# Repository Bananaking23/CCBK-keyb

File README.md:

# CCBK-keyb
I have decided to make this keyboard as I currently have a 68% keyboard and it feels bad not have f keys and home and delete, as I like to code and those keys are useful shortcuts. The switches I chose sound great and are relatively cheap. This project also improved my skills as I have only made a PCB ones (the hackpad). 

This is my berry cool 75% keyboard, it has a display, 80 keys, under-key lights, and a rotary encoder. It is powered by a rp2040 plus and uses an mcu23017 as gpio extender

# Photos

## almost full thing

for some reason i couldnt get all the keycaps on

## Scematic
### Main 

### Switch Matrix

### Led

## pcb

## Case

### Usb-c

### Plate

# BOM

### Link
https://1drv.ms/x/c/3f7de78506c0c654/IQBztQz0UetkR5LsrjEMn85vARuH-ncA3dCGhFmHGj_PK4U?e=rccWr9

#A fter completion

## Case

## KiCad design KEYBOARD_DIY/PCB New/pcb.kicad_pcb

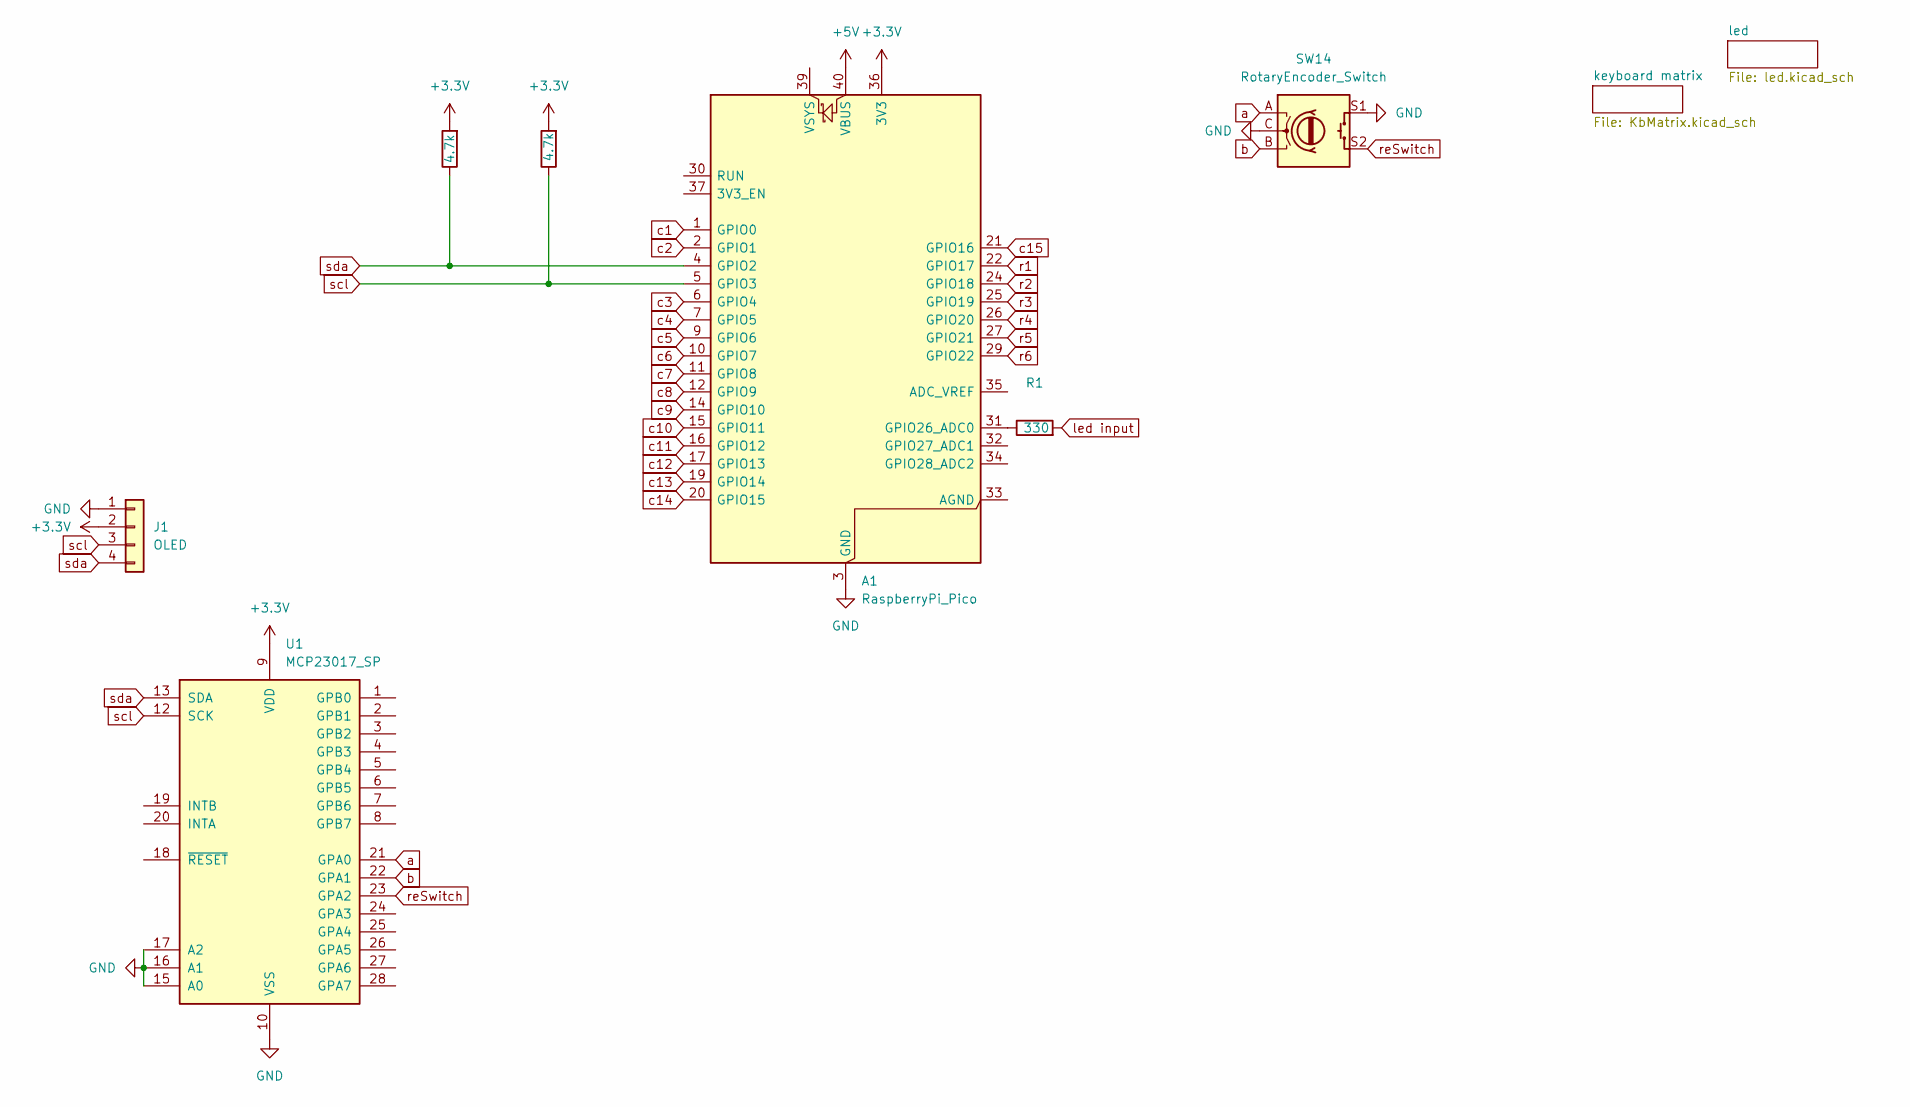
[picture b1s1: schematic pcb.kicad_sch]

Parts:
A1: RaspberryPi_Pico; RaspberryPi_Pico_Common_Unspecified
J1: OLED; SSD1306-0.91-OLED-4pin-128x32
R1: 330; R_Axial_DIN0207_L6.3mm_D2.5mm_P7.62mm_Horizontal
R2, R3: 4.7k; R_Axial_DIN0207_L6.3mm_D2.5mm_P7.62mm_Horizontal
SW14: RotaryEncoder_Switch; RotaryEncoder_Alps_EC11E-Switch_Vertical_H20mm
U1: MCP23017_SP; DIP-28_W7.62mm

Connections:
+3.3V: A1.36 (3V3), J1.2, R2.2, R3.2, U1.9 (VDD)
+5V: A1.40 (VBUS); also elsewhere on the board
GND: A1.3 (GND), A1.8 (GND), A1.13 (GND), A1.18 (GND), A1.23 (GND), A1.28 (GND), A1.38 (GND), J1.1, SW14.C, SW14.S1, U1.10 (VSS), U1.15 (A0), U1.16 (A1), U1.17 (A2); also elsewhere on the board
unnamed: A1.31 (GPIO26_ADC0), R1.1
a: SW14.A, U1.21 (GPA0)
b: SW14.B, U1.22 (GPA1)
c1: A1.1 (GPIO0); also elsewhere on the board
c2: A1.2 (GPIO1); also elsewhere on the board
c3: A1.6 (GPIO4); also elsewhere on the board
c4: A1.7 (GPIO5); also elsewhere on the board
c5: A1.9 (GPIO6); also elsewhere on the board
c6: A1.10 (GPIO7); also elsewhere on the board
c7: A1.11 (GPIO8); also elsewhere on the board
c8: A1.12 (GPIO9); also elsewhere on the board
c9: A1.14 (GPIO10); also elsewhere on the board
c10: A1.15 (GPIO11); also elsewhere on the board
c11: A1.16 (GPIO12); also elsewhere on the board
c12: A1.17 (GPIO13); also elsewhere on the board
c13: A1.19 (GPIO14); also elsewhere on the board
c14: A1.20 (GPIO15); also elsewhere on the board
c15: A1.21 (GPIO16); also elsewhere on the board
led input: R1.2; also elsewhere on the board
r1: A1.22 (GPIO17); also elsewhere on the board
r2: A1.24 (GPIO18); also elsewhere on the board
r3: A1.25 (GPIO19); also elsewhere on the board
r4: A1.26 (GPIO20); also elsewhere on the board
r5: A1.27 (GPIO21); also elsewhere on the board
r6: A1.29 (GPIO22); also elsewhere on the board
reSwitch: SW14.S2, U1.23 (GPA2)
scl: A1.5 (GPIO3), J1.3, R2.1, U1.12 (SCK)
sda: A1.4 (GPIO2), J1.4, R3.1, U1.13 (SDA)

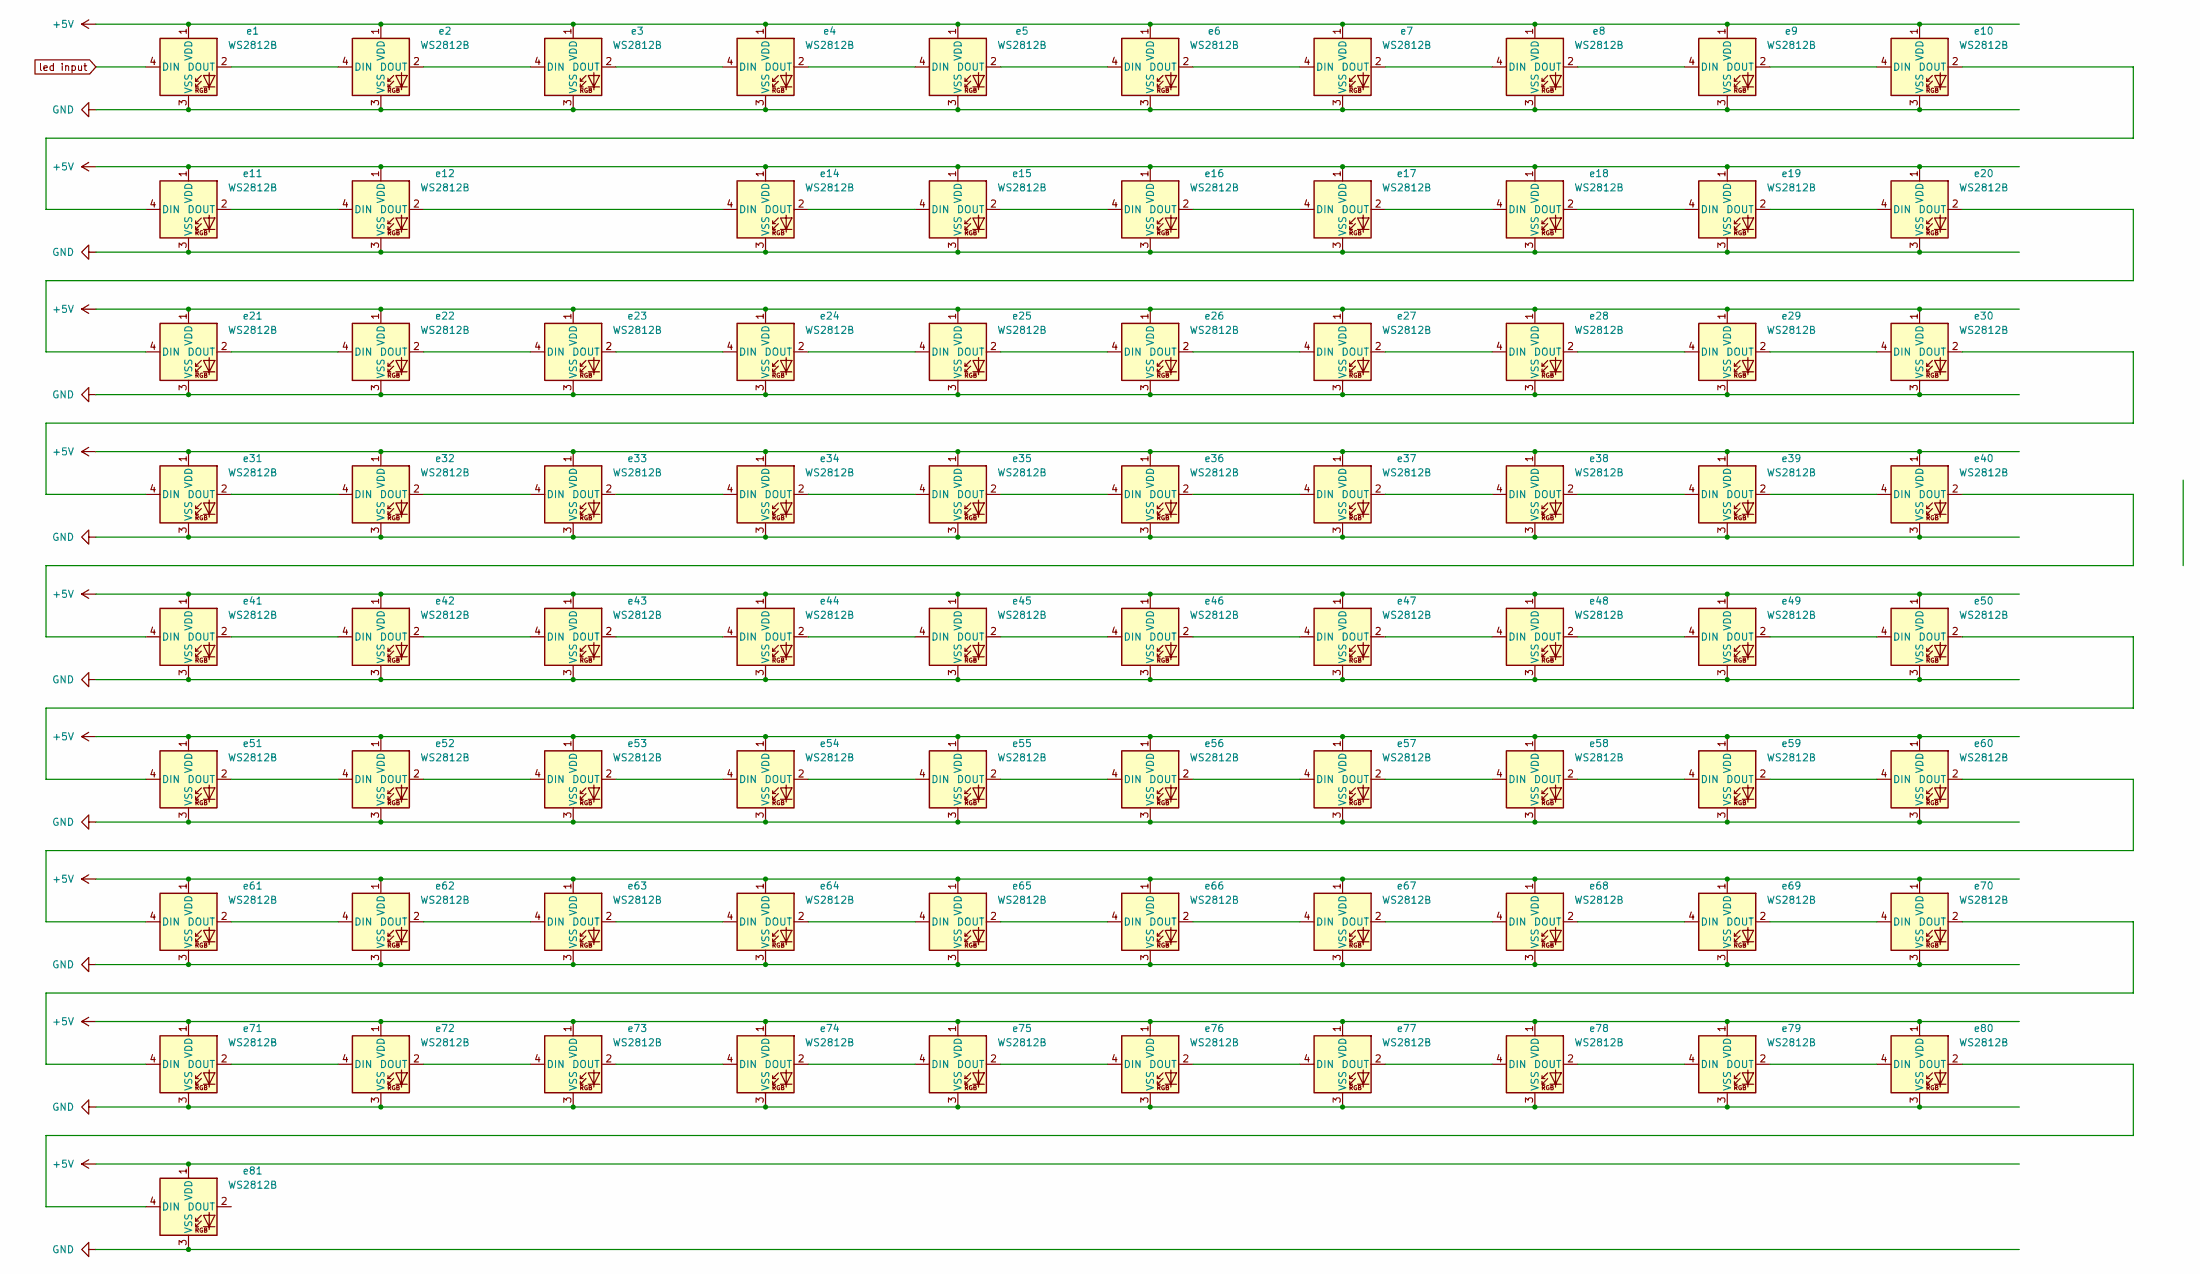
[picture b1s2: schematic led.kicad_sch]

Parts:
e1, e2, e3, e4, e5, e6, e7, e8, e9, e10, e11, e12, e14, e15, e16, e17, e18, e19, e20, e21, e22, e23, e24, e25, e26, e27, e28, e29, e30, e31, e32, e33, e34, e35, e36, e37, e38, e39, e40, e41, e42, e43, e44, e45, e46, e47, e48, e49, e50, e51, e52, e53, e54, e55, e56, e57, e58, e59, e60, e61, e62, e63, e64, e65, e66, e67, e68, e69, e70, e71, e72, e73, e74, e75, e76, e77, e78, e79, e80, e81: WS2812B; LED_SK6812MINI_PLCC4_3.5x3.5mm_P1.75mm

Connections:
+5V: e1.1 (VDD), e2.1 (VDD), e3.1 (VDD), e4.1 (VDD), e5.1 (VDD), e6.1 (VDD), e7.1 (VDD), e8.1 (VDD), e9.1 (VDD), e10.1 (VDD), e11.1 (VDD), e12.1 (VDD), e14.1 (VDD), e15.1 (VDD), e16.1 (VDD), e17.1 (VDD), e18.1 (VDD), e19.1 (VDD), e20.1 (VDD), e21.1 (VDD), e22.1 (VDD), e23.1 (VDD), e24.1 (VDD), e25.1 (VDD), e26.1 (VDD), e27.1 (VDD), e28.1 (VDD), e29.1 (VDD), e30.1 (VDD), e31.1 (VDD), e32.1 (VDD), e33.1 (VDD), e34.1 (VDD), e35.1 (VDD), e36.1 (VDD), e37.1 (VDD), e38.1 (VDD), e39.1 (VDD), e40.1 (VDD), e41.1 (VDD), e42.1 (VDD), e43.1 (VDD), e44.1 (VDD), e45.1 (VDD), e46.1 (VDD), e47.1 (VDD), e48.1 (VDD), e49.1 (VDD), e50.1 (VDD), e51.1 (VDD), e52.1 (VDD), e53.1 (VDD), e54.1 (VDD), e55.1 (VDD), e56.1 (VDD), e57.1 (VDD), e58.1 (VDD), e59.1 (VDD), e60.1 (VDD), e61.1 (VDD), e62.1 (VDD), e63.1 (VDD), e64.1 (VDD), e65.1 (VDD), e66.1 (VDD), e67.1 (VDD), e68.1 (VDD), e69.1 (VDD), e70.1 (VDD), e71.1 (VDD), e72.1 (VDD), e73.1 (VDD), e74.1 (VDD), e75.1 (VDD), e76.1 (VDD), e77.1 (VDD), e78.1 (VDD), e79.1 (VDD), e80.1 (VDD), e81.1 (VDD); also elsewhere on the board
GND: e1.3 (VSS), e2.3 (VSS), e3.3 (VSS), e4.3 (VSS), e5.3 (VSS), e6.3 (VSS), e7.3 (VSS), e8.3 (VSS), e9.3 (VSS), e10.3 (VSS), e11.3 (VSS), e12.3 (VSS), e14.3 (VSS), e15.3 (VSS), e16.3 (VSS), e17.3 (VSS), e18.3 (VSS), e19.3 (VSS), e20.3 (VSS), e21.3 (VSS), e22.3 (VSS), e23.3 (VSS), e24.3 (VSS), e25.3 (VSS), e26.3 (VSS), e27.3 (VSS), e28.3 (VSS), e29.3 (VSS), e30.3 (VSS), e31.3 (VSS), e32.3 (VSS), e33.3 (VSS), e34.3 (VSS), e35.3 (VSS), e36.3 (VSS), e37.3 (VSS), e38.3 (VSS), e39.3 (VSS), e40.3 (VSS), e41.3 (VSS), e42.3 (VSS), e43.3 (VSS), e44.3 (VSS), e45.3 (VSS), e46.3 (VSS), e47.3 (VSS), e48.3 (VSS), e49.3 (VSS), e50.3 (VSS), e51.3 (VSS), e52.3 (VSS), e53.3 (VSS), e54.3 (VSS), e55.3 (VSS), e56.3 (VSS), e57.3 (VSS), e58.3 (VSS), e59.3 (VSS), e60.3 (VSS), e61.3 (VSS), e62.3 (VSS), e63.3 (VSS), e64.3 (VSS), e65.3 (VSS), e66.3 (VSS), e67.3 (VSS), e68.3 (VSS), e69.3 (VSS), e70.3 (VSS), e71.3 (VSS), e72.3 (VSS), e73.3 (VSS), e74.3 (VSS), e75.3 (VSS), e76.3 (VSS), e77.3 (VSS), e78.3 (VSS), e79.3 (VSS), e80.3 (VSS), e81.3 (VSS); also elsewhere on the board
unnamed: e1.2 (DOUT), e2.4 (DIN)
unnamed: e2.2 (DOUT), e3.4 (DIN)
unnamed: e3.2 (DOUT), e4.4 (DIN)
unnamed: e4.2 (DOUT), e5.4 (DIN)
unnamed: e5.2 (DOUT), e6.4 (DIN)
unnamed: e6.2 (DOUT), e7.4 (DIN)
unnamed: e7.2 (DOUT), e8.4 (DIN)
unnamed: e8.2 (DOUT), e9.4 (DIN)
unnamed: e9.2 (DOUT), e10.4 (DIN)
unnamed: e10.2 (DOUT), e11.4 (DIN)
unnamed: e11.2 (DOUT), e12.4 (DIN)
unnamed: e12.2 (DOUT), e14.4 (DIN)
unnamed: e14.2 (DOUT), e15.4 (DIN)
unnamed: e15.2 (DOUT), e16.4 (DIN)
unnamed: e16.2 (DOUT), e17.4 (DIN)
unnamed: e17.2 (DOUT), e18.4 (DIN)
unnamed: e18.2 (DOUT), e19.4 (DIN)
unnamed: e19.2 (DOUT), e20.4 (DIN)
unnamed: e20.2 (DOUT), e21.4 (DIN)
unnamed: e21.2 (DOUT), e22.4 (DIN)
unnamed: e22.2 (DOUT), e23.4 (DIN)
unnamed: e23.2 (DOUT), e24.4 (DIN)
unnamed: e24.2 (DOUT), e25.4 (DIN)
unnamed: e25.2 (DOUT), e26.4 (DIN)
unnamed: e26.2 (DOUT), e27.4 (DIN)
unnamed: e27.2 (DOUT), e28.4 (DIN)
unnamed: e28.2 (DOUT), e29.4 (DIN)
unnamed: e29.2 (DOUT), e30.4 (DIN)
unnamed: e30.2 (DOUT), e31.4 (DIN)
unnamed: e31.2 (DOUT), e32.4 (DIN)
unnamed: e32.2 (DOUT), e33.4 (DIN)
unnamed: e33.2 (DOUT), e34.4 (DIN)
unnamed: e34.2 (DOUT), e35.4 (DIN)
unnamed: e35.2 (DOUT), e36.4 (DIN)
unnamed: e36.2 (DOUT), e37.4 (DIN)
unnamed: e37.2 (DOUT), e38.4 (DIN)
unnamed: e38.2 (DOUT), e39.4 (DIN)
unnamed: e39.2 (DOUT), e40.4 (DIN)
unnamed: e40.2 (DOUT), e41.4 (DIN)
unnamed: e41.2 (DOUT), e42.4 (DIN)
unnamed: e42.2 (DOUT), e43.4 (DIN)
unnamed: e43.2 (DOUT), e44.4 (DIN)
unnamed: e44.2 (DOUT), e45.4 (DIN)
unnamed: e45.2 (DOUT), e46.4 (DIN)
unnamed: e46.2 (DOUT), e47.4 (DIN)
unnamed: e47.2 (DOUT), e48.4 (DIN)
unnamed: e48.2 (DOUT), e49.4 (DIN)
unnamed: e49.2 (DOUT), e50.4 (DIN)
unnamed: e50.2 (DOUT), e51.4 (DIN)
unnamed: e51.2 (DOUT), e52.4 (DIN)
unnamed: e52.2 (DOUT), e53.4 (DIN)
unnamed: e53.2 (DOUT), e54.4 (DIN)
unnamed: e54.2 (DOUT), e55.4 (DIN)
unnamed: e55.2 (DOUT), e56.4 (DIN)
unnamed: e56.2 (DOUT), e57.4 (DIN)
unnamed: e57.2 (DOUT), e58.4 (DIN)
unnamed: e58.2 (DOUT), e59.4 (DIN)
unnamed: e59.2 (DOUT), e60.4 (DIN)
unnamed: e60.2 (DOUT), e61.4 (DIN)
unnamed: e61.2 (DOUT), e62.4 (DIN)
unnamed: e62.2 (DOUT), e63.4 (DIN)
unnamed: e63.2 (DOUT), e64.4 (DIN)
unnamed: e64.2 (DOUT), e65.4 (DIN)
unnamed: e65.2 (DOUT), e66.4 (DIN)
unnamed: e66.2 (DOUT), e67.4 (DIN)
unnamed: e67.2 (DOUT), e68.4 (DIN)
unnamed: e68.2 (DOUT), e69.4 (DIN)
unnamed: e69.2 (DOUT), e70.4 (DIN)
unnamed: e70.2 (DOUT), e71.4 (DIN)
unnamed: e71.2 (DOUT), e72.4 (DIN)
unnamed: e72.2 (DOUT), e73.4 (DIN)
unnamed: e73.2 (DOUT), e74.4 (DIN)
unnamed: e74.2 (DOUT), e75.4 (DIN)
unnamed: e75.2 (DOUT), e76.4 (DIN)
unnamed: e76.2 (DOUT), e77.4 (DIN)
unnamed: e77.2 (DOUT), e78.4 (DIN)
unnamed: e78.2 (DOUT), e79.4 (DIN)
unnamed: e79.2 (DOUT), e80.4 (DIN)
unnamed: e80.2 (DOUT), e81.4 (DIN)
led input: e1.4 (DIN); also elsewhere on the board

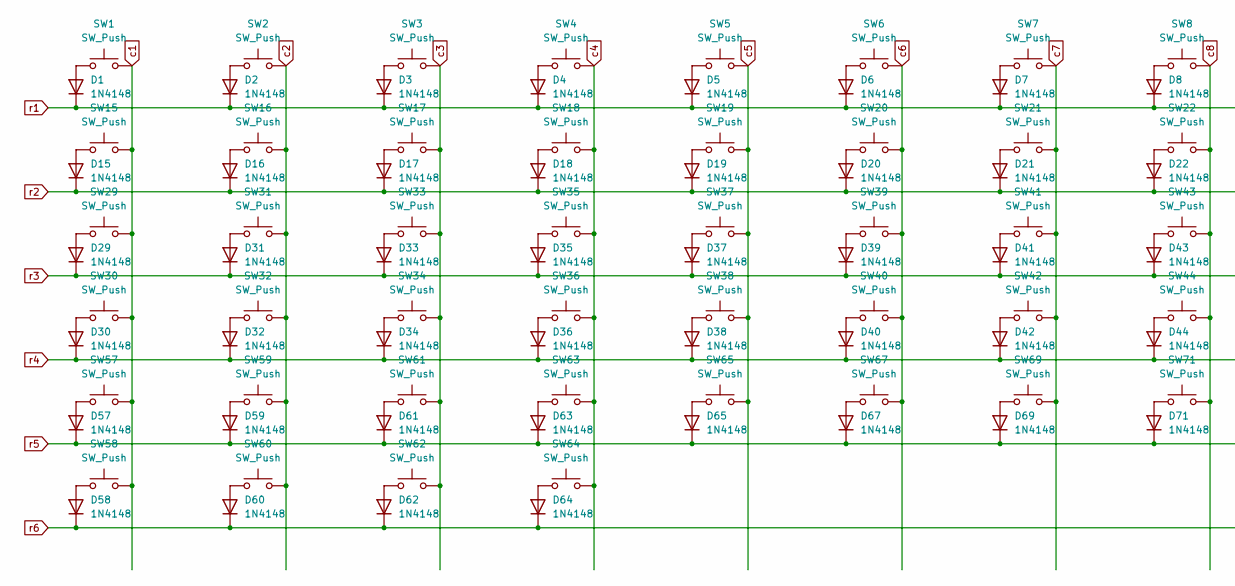
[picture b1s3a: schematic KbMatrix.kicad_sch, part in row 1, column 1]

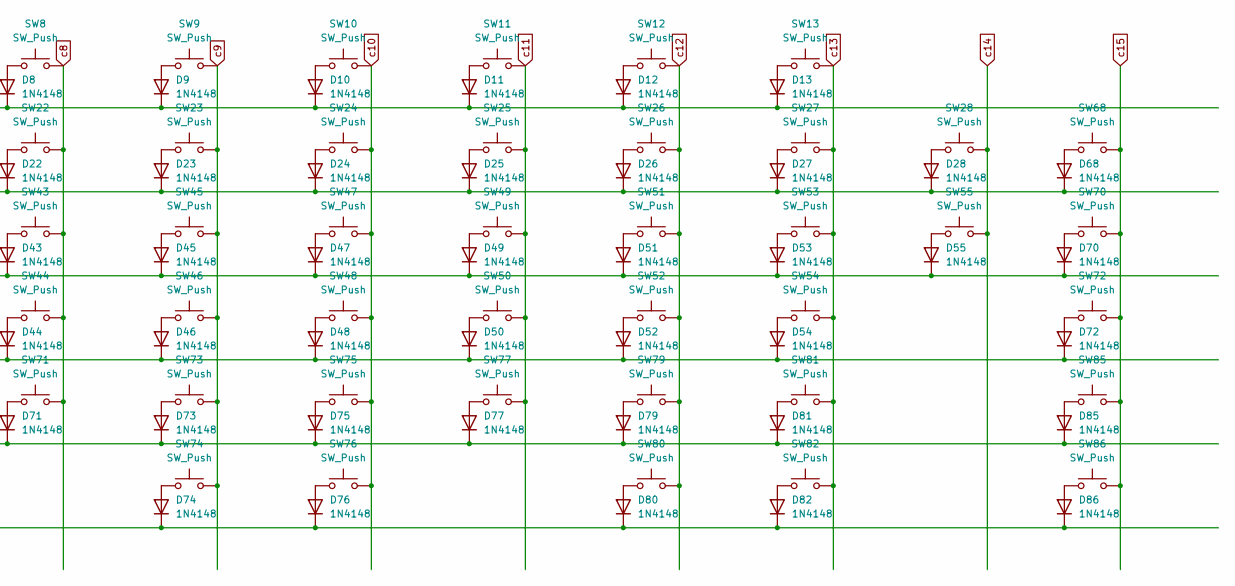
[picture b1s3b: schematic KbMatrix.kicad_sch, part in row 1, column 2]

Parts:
D1, D2, D3, D4, D5, D6, D7, D8, D9, D10, D11, D12, D13, D15, D16, D17, D18, D19, D20, D21, D22, D23, D24, D25, D26, D27, D28, D29, D30, D31, D32, D33, D34, D35, D36, D37, D38, D39, D40, D41, D42, D43, D44, D45, D46, D47, D48, D49, D50, D51, D52, D53, D54, D55, D57, D58, D59, D60, D61, D62, D63, D64, D65, D67, D68, D69, D70, D71, D72, D73, D74, D75, D76, D77, D79, D80, D81, D82, D85, D86: 1N4148; D_SOD-123
SW1, SW2, SW3, SW4, SW5, SW6, SW7, SW8, SW9, SW10, SW11, SW12, SW13, SW15, SW16, SW17, SW18, SW19, SW20, SW21, SW22, SW23, SW24, SW25, SW26, SW27, SW31, SW32, SW33, SW34, SW35, SW36, SW37, SW38, SW39, SW40, SW41, SW42, SW43, SW44, SW45, SW46, SW47, SW48, SW49, SW50, SW51, SW52, SW53, SW59, SW61, SW63, SW65, SW67, SW68, SW69, SW70, SW71, SW72, SW73, SW75, SW77, SW80, SW81, SW82, SW85, SW86: SW_Push; SW_Hotswap_Kailh_MX_Plated_1.00u_EDITED
SW28: SW_Push; SW_Hotswap_Kailh_MX_Plated_2.00u
SW29, SW55: SW_Push; SW_Hotswap_Kailh_MX_Plated_1.50u
SW30, SW79: SW_Push; SW_Hotswap_Kailh_MX_Plated_1.75u
SW54, SW57: SW_Push; SW_Hotswap_Kailh_MX_Plated_2.25u
SW58, SW60, SW62, SW74, SW76: SW_Push; SW_Hotswap_Kailh_MX_Plated_1.25u
SW64: SW_Push; SW_Hotswap_Kailh_MX_Plated_6.25u

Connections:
unnamed: D1.2 (A), SW1.1
unnamed: D2.2 (A), SW2.1
unnamed: D3.2 (A), SW3.1
unnamed: D4.2 (A), SW4.1
unnamed: D5.2 (A), SW5.1
unnamed: D6.2 (A), SW6.1
unnamed: D7.2 (A), SW7.1
unnamed: D8.2 (A), SW8.1
unnamed: D9.2 (A), SW9.1
unnamed: D10.2 (A), SW10.1
unnamed: D11.2 (A), SW11.1
unnamed: D12.2 (A), SW12.1
unnamed: D13.2 (A), SW13.1
unnamed: D15.2 (A), SW15.1
unnamed: D16.2 (A), SW16.1
unnamed: D17.2 (A), SW17.1
unnamed: D18.2 (A), SW18.1
unnamed: D19.2 (A), SW19.1
unnamed: D20.2 (A), SW20.1
unnamed: D21.2 (A), SW21.1
unnamed: D22.2 (A), SW22.1
unnamed: D23.2 (A), SW23.1
unnamed: D24.2 (A), SW24.1
unnamed: D25.2 (A), SW25.1
unnamed: D26.2 (A), SW26.1
unnamed: D27.2 (A), SW27.1
unnamed: D28.2 (A), SW28.1
unnamed: D29.2 (A), SW29.1
unnamed: D30.2 (A), SW30.1
unnamed: D31.2 (A), SW31.1
unnamed: D32.2 (A), SW32.1
unnamed: D33.2 (A), SW33.1
unnamed: D34.2 (A), SW34.1
unnamed: D35.2 (A), SW35.1
unnamed: D36.2 (A), SW36.1
unnamed: D37.2 (A), SW37.1
unnamed: D38.2 (A), SW38.1
unnamed: D39.2 (A), SW39.1
unnamed: D40.2 (A), SW40.1
unnamed: D41.2 (A), SW41.1
unnamed: D42.2 (A), SW42.1
unnamed: D43.2 (A), SW43.1
unnamed: D44.2 (A), SW44.1
unnamed: D45.2 (A), SW45.1
unnamed: D46.2 (A), SW46.1
unnamed: D47.2 (A), SW47.1
unnamed: D48.2 (A), SW48.1
unnamed: D49.2 (A), SW49.1
unnamed: D50.2 (A), SW50.1
unnamed: D51.2 (A), SW51.1
unnamed: D52.2 (A), SW52.1
unnamed: D53.2 (A), SW53.1
unnamed: D54.2 (A), SW54.1
unnamed: D55.2 (A), SW55.1
unnamed: D57.2 (A), SW57.1
unnamed: D58.2 (A), SW58.1
unnamed: D59.2 (A), SW59.1
unnamed: D60.2 (A), SW60.1
unnamed: D61.2 (A), SW61.1
unnamed: D62.2 (A), SW62.1
unnamed: D63.2 (A), SW63.1
unnamed: D64.2 (A), SW64.1
unnamed: D65.2 (A), SW65.1
unnamed: D67.2 (A), SW67.1
unnamed: D68.2 (A), SW68.1
unnamed: D69.2 (A), SW69.1
unnamed: D70.2 (A), SW70.1
unnamed: D71.2 (A), SW71.1
unnamed: D72.2 (A), SW72.1
unnamed: D73.2 (A), SW73.1
unnamed: D74.2 (A), SW74.1
unnamed: D75.2 (A), SW75.1
unnamed: D76.2 (A), SW76.1
unnamed: D77.2 (A), SW77.1
unnamed: D79.2 (A), SW79.1
unnamed: D80.2 (A), SW80.1
unnamed: D81.2 (A), SW81.1
unnamed: D82.2 (A), SW82.1
unnamed: D85.2 (A), SW85.1
unnamed: D86.2 (A), SW86.1
c1: SW1.2, SW15.2, SW29.2, SW30.2, SW57.2, SW58.2; also elsewhere on the board
c2: SW2.2, SW16.2, SW31.2, SW32.2, SW59.2, SW60.2; also elsewhere on the board
c3: SW3.2, SW17.2, SW33.2, SW34.2, SW61.2, SW62.2; also elsewhere on the board
c4: SW4.2, SW18.2, SW35.2, SW36.2, SW63.2, SW64.2; also elsewhere on the board
c5: SW5.2, SW19.2, SW37.2, SW38.2, SW65.2; also elsewhere on the board
c6: SW6.2, SW20.2, SW39.2, SW40.2, SW67.2; also elsewhere on the board
c7: SW7.2, SW21.2, SW41.2, SW42.2, SW69.2; also elsewhere on the board
c8: SW8.2, SW22.2, SW43.2, SW44.2, SW71.2; also elsewhere on the board
c9: SW9.2, SW23.2, SW45.2, SW46.2, SW73.2, SW74.2; also elsewhere on the board
c10: SW10.2, SW24.2, SW47.2, SW48.2, SW75.2, SW76.2; also elsewhere on the board
c11: SW11.2, SW25.2, SW49.2, SW50.2, SW77.2; also elsewhere on the board
c12: SW12.2, SW26.2, SW51.2, SW52.2, SW79.2, SW80.2; also elsewhere on the board
c13: SW13.2, SW27.2, SW53.2, SW54.2, SW81.2, SW82.2; also elsewhere on the board
c14: SW28.2, SW55.2; also elsewhere on the board
c15: SW68.2, SW70.2, SW72.2, SW85.2, SW86.2; also elsewhere on the board
r1: D1.1 (K), D2.1 (K), D3.1 (K), D4.1 (K), D5.1 (K), D6.1 (K), D7.1 (K), D8.1 (K), D9.1 (K), D10.1 (K), D11.1 (K), D12.1 (K), D13.1 (K); also elsewhere on the board
r2: D15.1 (K), D16.1 (K), D17.1 (K), D18.1 (K), D19.1 (K), D20.1 (K), D21.1 (K), D22.1 (K), D23.1 (K), D24.1 (K), D25.1 (K), D26.1 (K), D27.1 (K), D28.1 (K), D68.1 (K); also elsewhere on the board
r3: D29.1 (K), D31.1 (K), D33.1 (K), D35.1 (K), D37.1 (K), D39.1 (K), D41.1 (K), D43.1 (K), D45.1 (K), D47.1 (K), D49.1 (K), D51.1 (K), D53.1 (K), D55.1 (K), D70.1 (K); also elsewhere on the board
r4: D30.1 (K), D32.1 (K), D34.1 (K), D36.1 (K), D38.1 (K), D40.1 (K), D42.1 (K), D44.1 (K), D46.1 (K), D48.1 (K), D50.1 (K), D52.1 (K), D54.1 (K), D72.1 (K); also elsewhere on the board
r5: D57.1 (K), D59.1 (K), D61.1 (K), D63.1 (K), D65.1 (K), D67.1 (K), D69.1 (K), D71.1 (K), D73.1 (K), D75.1 (K), D77.1 (K), D79.1 (K), D81.1 (K), D85.1 (K); also elsewhere on the board
r6: D58.1 (K), D60.1 (K), D62.1 (K), D64.1 (K), D74.1 (K), D76.1 (K), D80.1 (K), D82.1 (K), D86.1 (K); also elsewhere on the board

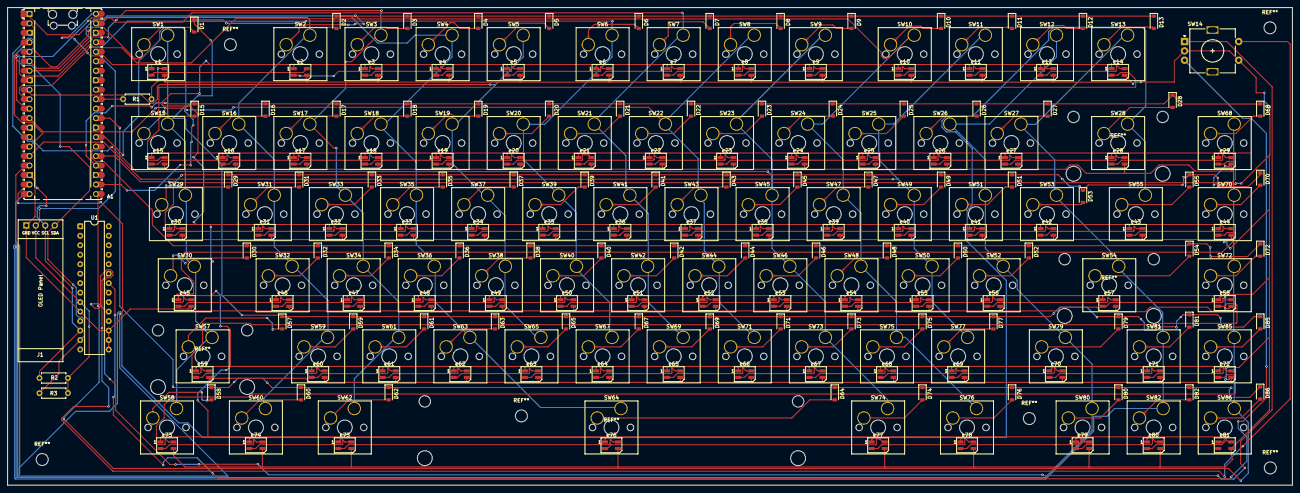
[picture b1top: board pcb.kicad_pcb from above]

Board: 2 copper layers, 344.2 x 128.0 mm, 247 parts (0 on the bottom side), 190 nets.

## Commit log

2026-01-24 Update README with project details and images
    Added detailed description and images for the CCBK-keyb project.
2026-01-24 Enhance keyboard description in README
    Updated description to include rotary encoder and gpio extender.
2026-01-24 Update BOM image and link in README
    Updated BOM image and link in README.
2026-01-24 Remove price details from README
    Removed total price mention from the README.
2026-01-25 added all
2026-01-25 Update images in README.md for schematic and PCB
2026-01-25 added all fils
2026-02-15 Replace images in README.md and update PCB section
2026-02-15 Revise case section and add new images
    Updated images and sections in the README to reflect changes in the case design.
